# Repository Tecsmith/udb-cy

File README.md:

# Unified Daughterboard CY

> Based on https://github.com/Unified-Daughterboard/UDB-C-Legacy  
> &copy; 2019 ai03

The Unified Daughterboard is an open standard to unify the USB daughterboards used in custom mechanical keyboard projects.

## This spinoff 

The UDB project has progressed to 3 distinct variants:
- C-JSH with JST PH connector
- C-EZM with Molex Pico-EZmate connector
- and a thinner variant S, also with EZmate connector

These new C5 variants has opted to merge shield grounding and cable ground, but this variant is more cautious on case/cable grounding and protects the circuit ground with a 4.7 µF capacitor and a 1 MΩ resistor that are used as a **common EMI (Electromagnetic Interference) and ESD (Electrostatic Discharge) filtering network**.

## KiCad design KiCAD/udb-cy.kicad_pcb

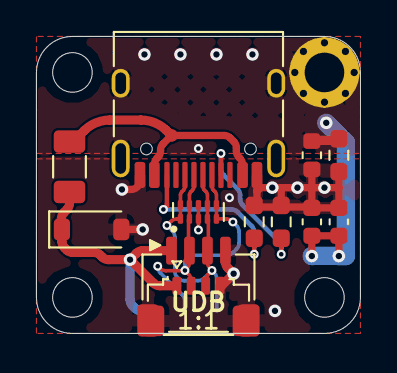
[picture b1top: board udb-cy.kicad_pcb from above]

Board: 4 copper layers, 18.0 x 16.5 mm, 17 parts (1 on the bottom side), 8 nets.

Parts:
C1: 0.1µF; C_0603_1608Metric
C2: 1nF; C_0603_1608Metric
D1: SMF9.0CA; D_SOD-123
F1: ASMD1206-150; Fuse_1206_3216Metric
FB1: 600Ω @ 100MHz; L_0603_1608Metric
H1: Mount_M2_Rel
H2, H3, H4: Hole_M2
J0: USB_C_Receptacle; USB_C_Receptacle_HRO_TYPE-C-31-M-12
J1: JST-SH-04; JST_SH_SM04B-SRSS-TB_1x04-1MP_P1.00mm_Horizontal
J2: JST-SUR-04; JST_SUR_SM04B-SURS-TF_1x04-1MP_P0.80mm_Horizontal
J3: Conn_01x04; 1x04_P2.54mm_SolderPads
R1, R2: 5.1K; R_0603_1608Metric_Pad0.98x0.95mm_HandSolder
R3: 1M; R_0603_1608Metric_Pad0.98x0.95mm_HandSolder
Z1: TPD4E05U06DQAR; UFDFN-10_2.5x1.0mm_P0.5mm

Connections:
D+: J0.A6 (D+), J0.B6 (D+), J1.3, J2.3 (_3), J3.3, Z1.1, Z1.4, Z1.7, Z1.10
D-: J0.A7 (D-), J0.B7 (D-), J1.2, J2.2 (_2), J3.2, Z1.2, Z1.5, Z1.6, Z1.9
Earth: C1.1, C2.1, FB1.1, H1.MP, J0.SH (SHIELD), R3.1
GND: C1.2, C2.2, D1.2 (A2), FB1.2, J0.A1 (GND), J0.A12 (GND), J0.B1 (GND), J0.B12 (GND), J1.4, J1.MP, J2.4 (_4), J2.MP, J3.4, R1.2, R2.2, R3.2, Z1.3, Z1.8
unnamed: J0.A5 (CC1), R1.1
unnamed: J0.B5 (CC2), R2.1
VBUS: F1.1, J0.A4 (VBUS), J0.A9 (VBUS), J0.B4 (VBUS), J0.B9 (VBUS)
VCC: D1.1 (A1), F1.2, J1.1, J2.1 (_1), J3.1

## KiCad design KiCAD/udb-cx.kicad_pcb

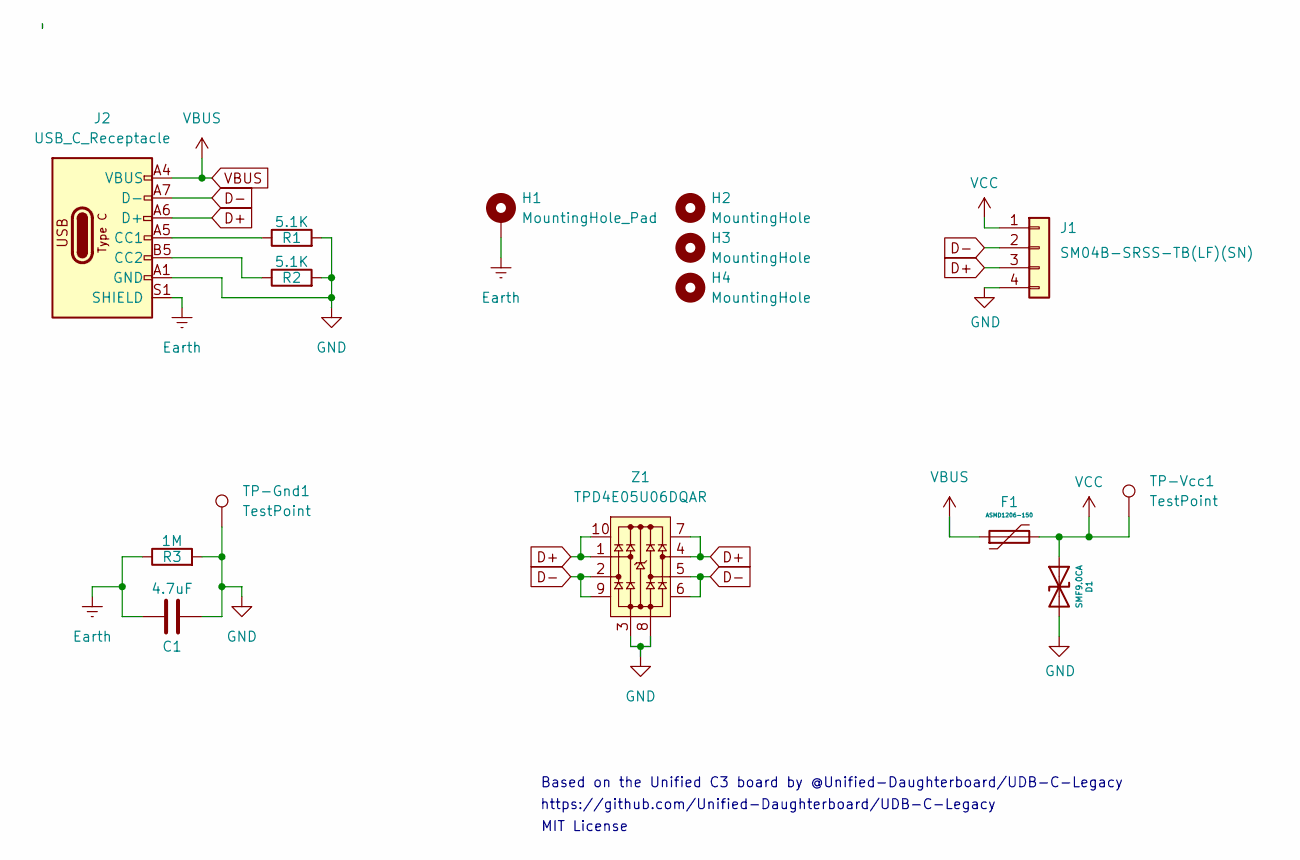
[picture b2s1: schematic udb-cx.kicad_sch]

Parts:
C1: 4.7uF; C_0603_1608Metric
D1: SMF9.0CA; D_SOD-123; Manufacturer Part No SMF9.0CA; LCSC Part No C123799
F1: ASMD1206-150; Fuse_1206_3216Metric; Manufacturer Part No ASMD1206-150; LCSC Part No C135342
H1: MountingHole_Pad; MountingHole_2.2mm_M2_Pad
H2, H3, H4: MountingHole; MountingHole_2.2mm_M2
J1: SM04B-SRSS-TB(LF)(SN); JST_SH_SM04B-SRSS-TB_1x04-1MP_P1.00mm_Horizontal; Manufacturer Part No SM04B-SRSS-TB(LF)(SN); LCSC Part No C160404
J2: USB_C_Receptacle; USB_C_Receptacle_HRO_TYPE-C-31-M-12
R1, R2: 5.1K; R_0603
R3: 1M; R_0603
TP-Gnd1: TestPoint; TestPoint_Pad_1.5x1.5mm
TP-Vcc1: TestPoint; TestPoint_Pad_1.5x1.5mm
Z1: TPD4E05U06DQAR; UFDFN-10_2.5x1.0mm_P0.5mm

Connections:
D+: J1.3, J2.A6 (D+), J2.B6 (D+), Z1.1, Z1.4, Z1.7, Z1.10
D-: J1.2, J2.A7 (D-), J2.B7 (D-), Z1.2, Z1.5, Z1.6, Z1.9
Earth: C1.1, H1.1, J2.S1 (SHIELD), R3.1
GND: C1.2, D1.2 (A2), J1.4, J1.MP, J2.A1 (GND), J2.A12 (GND), J2.B1 (GND), J2.B12 (GND), R1.2, R2.2, R3.2, TP-Gnd1.1, Z1.3, Z1.8
unnamed: J2.A5 (CC1), R1.1
unnamed: J2.B5 (CC2), R2.1
VBUS: F1.1, J2.A4 (VBUS), J2.A9 (VBUS), J2.B4 (VBUS), J2.B9 (VBUS)
VCC: D1.1 (A1), F1.2, J1.1, TP-Vcc1.1

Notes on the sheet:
MIT License
Based on the Unified C3 board by @Unified-Daughterboard/UDB-C-Legacy
https://github.com/Unified-Daughterboard/UDB-C-Legacy

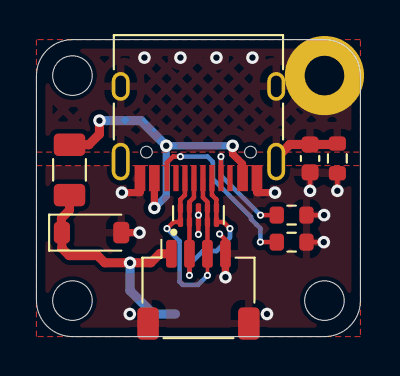
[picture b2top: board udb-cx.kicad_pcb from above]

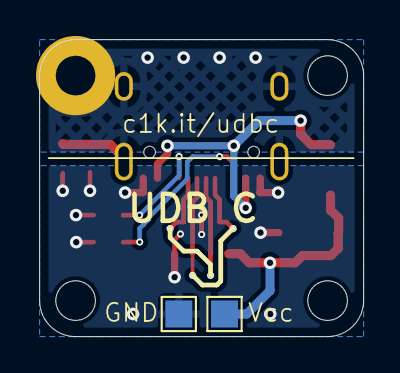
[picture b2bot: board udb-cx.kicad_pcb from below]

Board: 4 copper layers, 18.0 x 16.5 mm, 15 parts (2 on the bottom side), 8 nets.

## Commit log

2025-11-06 fist upload
2025-11-08 mil sized traces
2025-11-10 Added JST SUR connector option
2025-11-14 Expose all 4 pins on the underside
2025-11-20 update-2025-11-20
